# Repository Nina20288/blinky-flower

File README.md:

# blinky-flower
A flower shaped LED chaser that blinks 5 LEDs in a variable speed sequence. 

Here is the image of the 3D view: 

Order checkout:

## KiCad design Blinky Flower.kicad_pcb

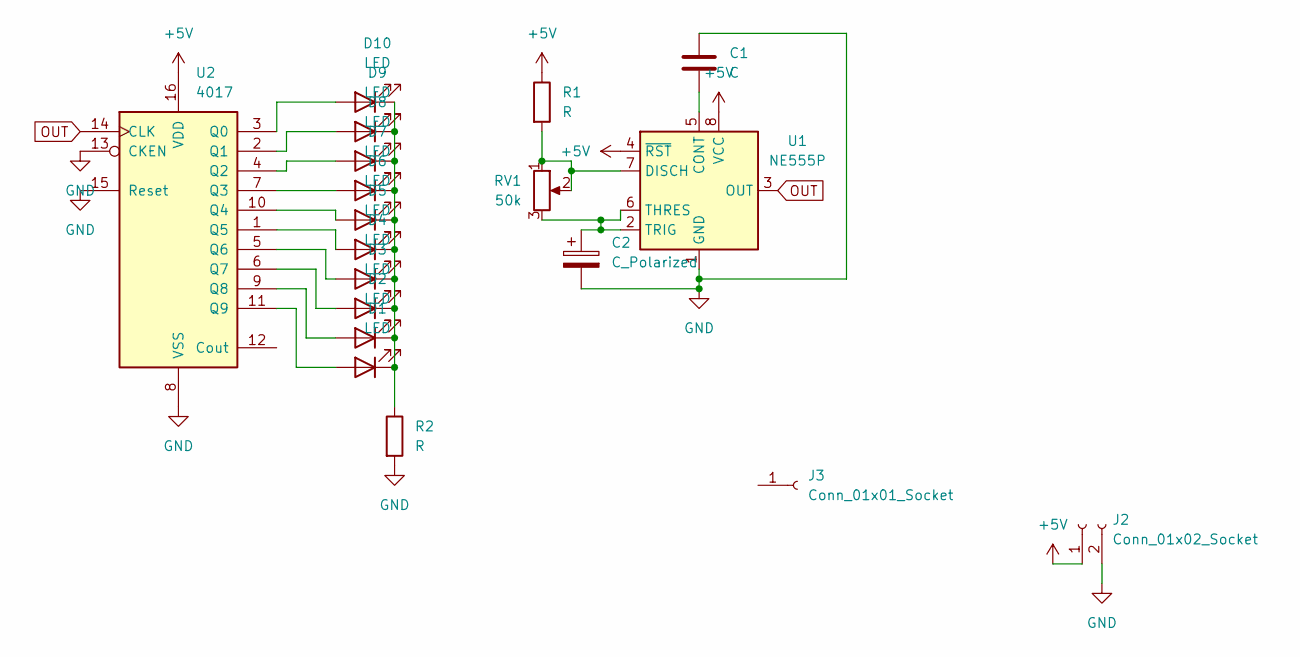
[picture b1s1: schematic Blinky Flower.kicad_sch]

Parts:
C1: C; CP_Radial_D5.0mm_P2.00mm
C2: C_Polarized; C_Disc_D7.5mm_W2.5mm_P5.00mm
D1, D2, D3, D4, D5, D6, D7, D8, D9, D10: LED; LED_D5.0mm
J2: Conn_01x02_Socket; PinHeader_1x02_P2.54mm_Vertical
J3: Conn_01x01_Socket; PinHeader_1x01_P2.54mm_Vertical
R1, R2: R; R_Axial_DIN0207_L6.3mm_D2.5mm_P7.62mm_Horizontal
RV1: 50k; Potentiometer_Vishay_T93YA_Vertical
U1: NE555P; DIP-8_W7.62mm
U2: 4017; DIP-16_W7.62mm

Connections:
+5V: J2.1, R1.1, U1.4 (~RST), U1.8 (VCC), U2.16 (VDD)
GND: C1.1, C2.2, J2.2, R2.2, U1.1 (GND), U2.8 (VSS), U2.13 (CKEN), U2.15 (Reset)
unnamed: D1.2 (A), U2.11 (Q9)
unnamed: D1.1 (K), D2.1 (K), D3.1 (K), D4.1 (K), D5.1 (K), D6.1 (K), D7.1 (K), D8.1 (K), D9.1 (K), D10.1 (K), R2.1
unnamed: D2.2 (A), U2.9 (Q8)
unnamed: D3.2 (A), U2.6 (Q7)
unnamed: D4.2 (A), U2.5 (Q6)
unnamed: D5.2 (A), U2.1 (Q5)
unnamed: D6.2 (A), U2.10 (Q4)
unnamed: D7.2 (A), U2.7 (Q3)
unnamed: D8.2 (A), U2.4 (Q2)
unnamed: D9.2 (A), U2.2 (Q1)
unnamed: D10.2 (A), U2.3 (Q0)
unnamed: C1.2, U1.5 (CONT)
unnamed: R1.2, RV1.1, RV1.2, U1.7 (DISCH)
unnamed: C2.1, RV1.3, U1.2 (TRIG), U1.6 (THRES)
OUT: U1.3 (OUT), U2.14 (CLK)

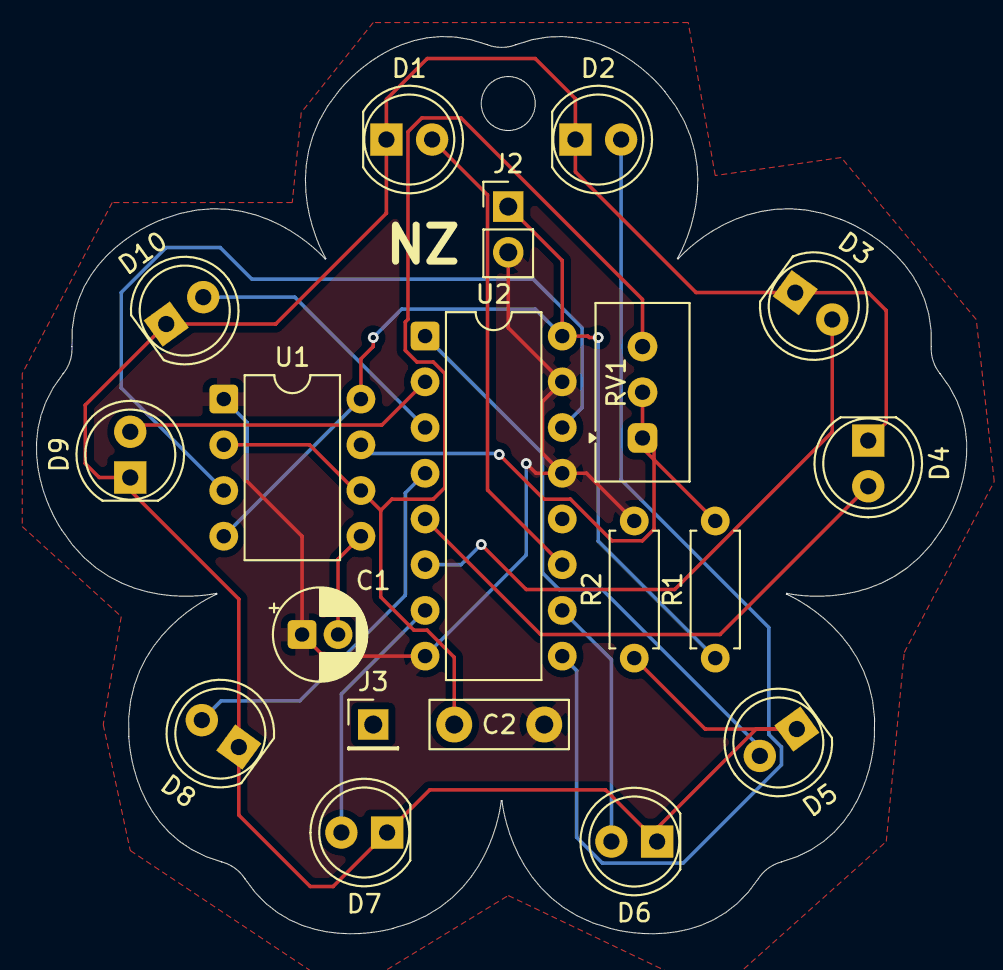
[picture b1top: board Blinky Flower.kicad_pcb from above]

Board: 2 copper layers, 51.7 x 49.8 mm, 19 parts (0 on the bottom side), 17 nets.

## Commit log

2026-04-24 3d image
2026-04-24 more files
    .kicad_pro
    .kicad_sch
    .kicad_pcb
2026-04-24 gerbers
2026-04-24 order pcb
2026-04-24 pcb checkout
2026-04-25 Update README with images and order information
    Added images for 3D view and order checkout.
2026-04-25 Add second image for order checkout section
2026-04-25 updated gerbers
2026-04-25 update files
